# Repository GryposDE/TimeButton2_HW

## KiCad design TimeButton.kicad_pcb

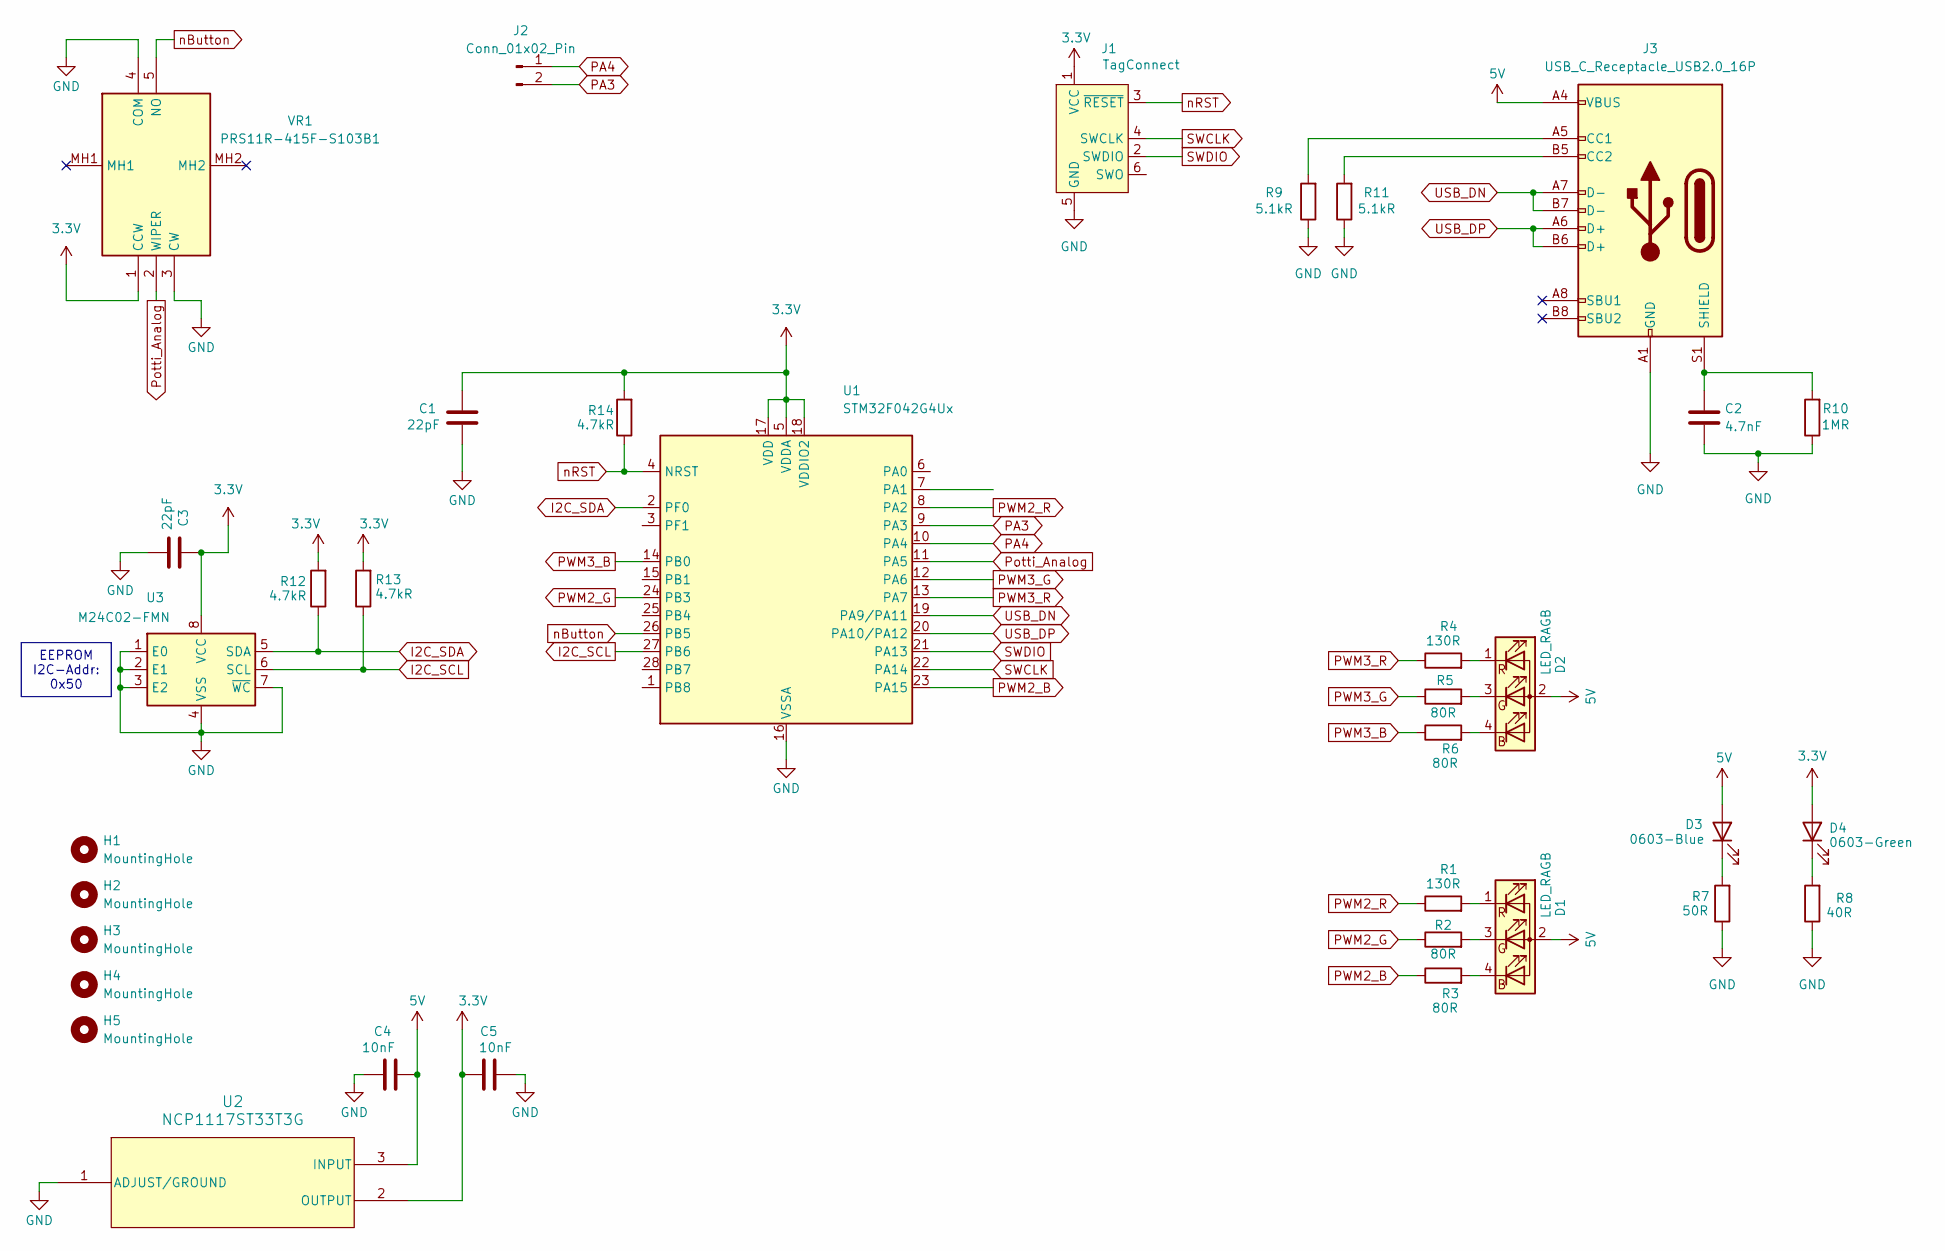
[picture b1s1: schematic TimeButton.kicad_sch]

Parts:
C1, C3: 22pF; C_0805_2012Metric
C2: 4.7nF; C_0805_2012Metric_Pad1.18x1.45mm_HandSolder
C4, C5: 10nF; C_0805_2012Metric
D1, D2: LED_RAGB; LED_D5.0mm-4_RGB_Wide_Pins
D3: 0603-Blue; LED_0805_2012Metric_Pad1.15x1.40mm_HandSolder
D4: 0603-Green; LED_0805_2012Metric_Pad1.15x1.40mm_HandSolder
H1, H2, H3, H4, H5: MountingHole; MountingHole_2.2mm_M2_DIN965
J1: TagConnect; Tag-Connect_TC2030-IDC-NL_2x03_P1.27mm_Vertical
J2: Conn_01x02_Pin; PinHeader_1x02_P2.54mm_Vertical
J3: USB_C_Receptacle_USB2.0_16P; USB_C_Receptacle_G-Switch_GT-USB-7010ASV
R1, R4: 130R; R_0805_2012Metric_Pad1.20x1.40mm_HandSolder
R2, R3, R5, R6: 80R; R_0805_2012Metric_Pad1.20x1.40mm_HandSolder
R7: 50R; R_0805_2012Metric_Pad1.20x1.40mm_HandSolder
R8: 40R; R_0805_2012Metric_Pad1.20x1.40mm_HandSolder
R9, R11: 5.1kR; R_0805_2012Metric_Pad1.20x1.40mm_HandSolder
R10: 1MR; R_0805_2012Metric_Pad1.20x1.40mm_HandSolder
R12, R13, R14: 4.7kR; R_0805_2012Metric_Pad1.20x1.40mm_HandSolder
U1: STM32F042G4Ux; QFN-28_4x4mm_P0.5mm
U2: NCP1117ST33T3G; SOT223-3_ONS
U3: M24C02-FMN; SOIC-8_3.9x4.9mm_P1.27mm
VR1: PRS11R-415F-S103B1; PRS11R415FS103B1; Mouser Part Number 652-PRS11R415FS103B1

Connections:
3.3V: C1.2, C3.2, C5.1, D4.2 (A), J1.1 (VCC), R12.2, R13.2, R14.2, U1.5 (VDDA), U1.17 (VDD), U1.18 (VDDIO2), U2.2 (OUTPUT), U3.8 (VCC), VR1.1 (CCW)
5V: C4.2, D1.2 (A), D2.2 (A), D3.2 (A), J3.A4 (VBUS), J3.A9 (VBUS), J3.B4 (VBUS), J3.B9 (VBUS), U2.3 (INPUT)
GND: C1.1, C2.2, C3.1, C4.1, C5.2, J1.5 (GND), J3.A1 (GND), J3.A12 (GND), J3.B1 (GND), J3.B12 (GND), R7.1, R8.1, R9.1, R10.1, R11.1, U1.16 (VSSA), U2.1 (ADJUST/GROUND), U3.1 (E0), U3.2 (E1), U3.3 (E2), U3.4 (VSS), U3.7 (~WC), VR1.3 (CW), VR1.4 (COM)
I2C_SCL: R13.1, U1.27 (PB6), U3.6 (SCL)
I2C_SDA: R12.1, U1.2 (PF0), U3.5 (SDA)
unnamed: D1.4 (BK), R3.2
unnamed: D1.3 (GK), R2.2
unnamed: D1.1 (RK), R1.2
unnamed: D2.4 (BK), R6.2
unnamed: D2.3 (GK), R5.2
unnamed: D2.1 (RK), R4.2
unnamed: D3.1 (K), R7.2
unnamed: D4.1 (K), R8.2
unnamed: J3.A5 (CC1), R9.2
unnamed: J3.B5 (CC2), R11.2
unnamed: C2.1, J3.S1 (SHIELD), R10.2
PA3: J2.2, U1.9 (PA3)
PA4: J2.1, U1.10 (PA4)
PWM2_B: R3.1, U1.23 (PA15)
PWM2_G: R2.1, U1.24 (PB3)
PWM2_R: R1.1, U1.8 (PA2)
PWM3_B: R6.1, U1.14 (PB0)
PWM3_G: R5.1, U1.12 (PA6)
PWM3_R: R4.1, U1.13 (PA7)
Potti_Analog: U1.11 (PA5), VR1.2 (WIPER)
SWCLK: J1.4 (SWCLK), U1.22 (PA14)
SWDIO: J1.2 (SWDIO), U1.21 (PA13)
USB_DN: J3.A7 (D-), J3.B7 (D-), U1.19 (PA9/PA11)
USB_DP: J3.A6 (D+), J3.B6 (D+), U1.20 (PA10/PA12)
nButton: U1.26 (PB5), VR1.5 (NO)
nRST: J1.3 (~RESET), R14.1, U1.4 (NRST)

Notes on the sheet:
EEPROM I2C-Addr: 0x50

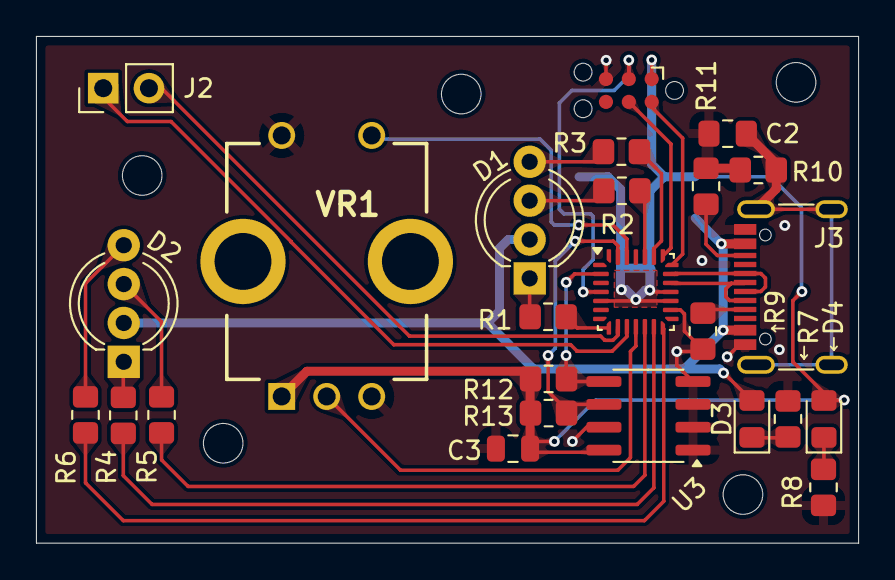
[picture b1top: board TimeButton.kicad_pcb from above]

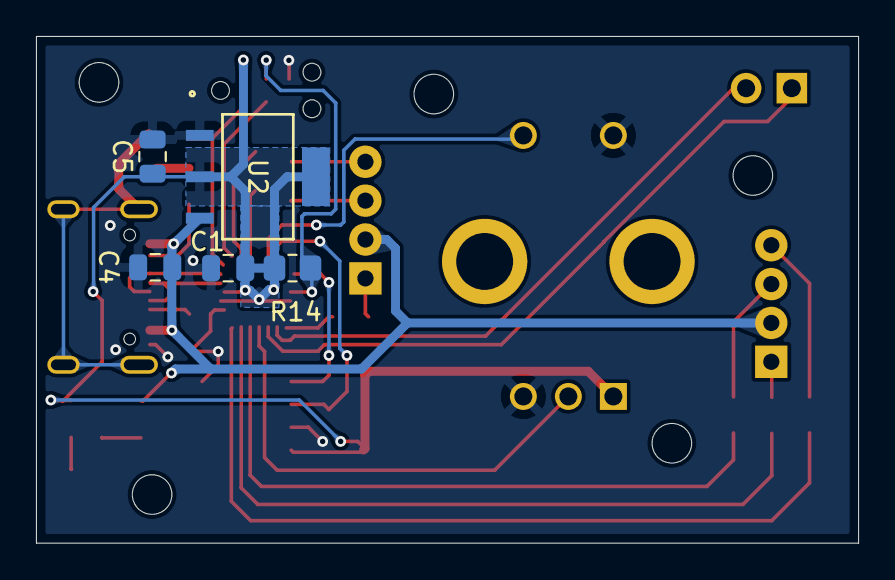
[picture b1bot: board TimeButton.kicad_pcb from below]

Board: 2 copper layers, 45.7 x 28.2 mm, 35 parts (5 on the bottom side), 31 nets.

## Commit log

2025-07-27 v1.0
2025-07-27 Added two GPIO Connectors for additional use
2025-08-02 Added Capacitor for EEPROM
2025-08-02 Added jpg pics of PCB
2025-08-02 Added gitignore and removed backup zips
